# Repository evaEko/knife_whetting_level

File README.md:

# Knife Level BLUNT

A small digital level for knife sharpening. Measures blade surface inclination in real time, displays the angle, and alerts you when you drift from your target sharpening angle.

 Built on MicroPython running on an nRF52840 microcontroller.

Here are some vids:
* [demo vid of the sensor responsiveness](https://imgur.com/a/BOzFHaE).
* [demo vid of the Android app](https://i.imgur.com/QXUnDTm.mp4).
* [foolish idea with 2 displays](https://i.imgur.com/3KEsX2l.mp4)

Commercial use and resale are not permitted.

## License

- Software code, documentation, images, and hardware design files: [CC BY-NC 4.0](LICENSE)
- Third-party subcomponents may use their own license where noted (for example, `kicad/nice-nano-kicad/`)

### Third-party notices

- `kicad/nice-nano-kicad/` is a third-party nice!nano symbol/footprint library bundled with this project.
- The bundled library declares `GNU GPLv3` in `kicad/nice-nano-kicad/README.md`; keep that notice and attribution when redistributing those files.

> **Disclaimer:** This project is provided as-is, without warranty of any kind. The author is not liable for any damage, injury, or loss arising from the use, misuse, or inability to use this project or any hardware built from it.

## Getting Started

1. [Assemble the hardware](docs/HOW_TO_HARDWARE.md)
2. [Flash the firmware](docs/HOW_TO_FIRMWARE.md)
3. Optionally install the Android companion app from the `knife_level_android_apk` workflow artifact

If impatient, go over to [Quick Start](docs/QUICK_START.md).

## Known Issues

- **Android app rescan after restart** — if you power-cycle the level, the Android app will not reconnect automatically; open the app and scan again.
- **Lifted detection is experimental** — the feature that detects when the blade leaves the stone is not reliable and may produce false positives or miss lift events; treat alerts that depend on it as best-effort.

## Acknowledgements

Thanks to [jkorte-dev](https://github.com/jkorte-dev) for publishing the nRF52840 SuperMini/Nice!Nano MicroPython board definitions and UF2 builds used as a flashing base.

Development was assisted by [Claude](https://claude.ai) (Anthropic).

## Features

- **Live sharpening angle** — displays current blade surface inclination in real time on the OLED, rounded to nearest 0.5° with one decimal place
- **Rotation-invariant measurement** — the sensor attaches to the blade with a magnet and can spin freely on the blade face; the reading reports the correct blade angle regardless of how the sensor is rotated on the surface
- **Session calibration** — set the current surface as zero from the on-device settings menu or the Android app
- **Angle setting** — set the current angle as the sharpening angle
- **Visual alert** — display inverts when you drift more than the configured threshold from the target angle; both 0° and 180° orientations are treated as equivalent (knife flipped upside-down is the same angle); threshold supports decimal values (e.g. 0.5°)
- **Preset angle profiles** — define named knives and their angles in `angles.csv`; select them on-device with the top button, with optional restore of the last selected preset after reboot
- **Calibration + presets are independent** — calibrate once to set your physical reference point (zero), then switch between knife presets freely; each preset angle is always displayed relative to the calibration, never compounding
- **Bluetooth companion app** — configure display/behavior settings over BLE, calibrate from the phone, manage preset angles with CRUD operations, and back up/restore presets plus app-exposed settings after reflashing

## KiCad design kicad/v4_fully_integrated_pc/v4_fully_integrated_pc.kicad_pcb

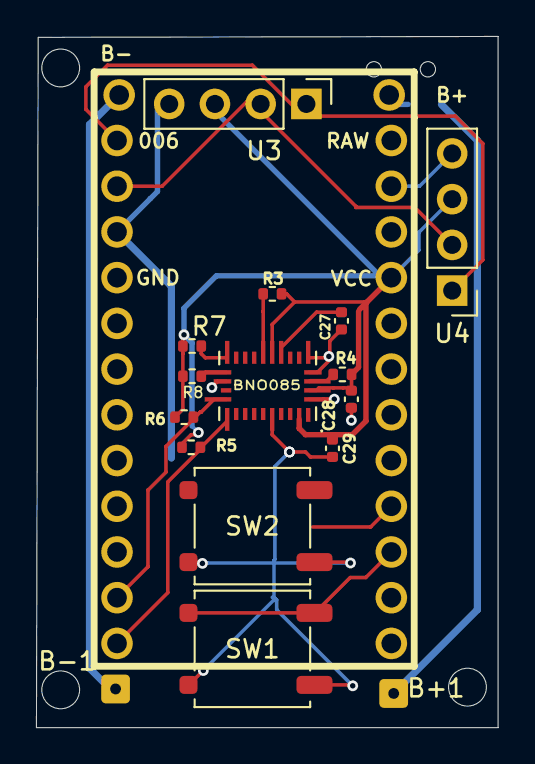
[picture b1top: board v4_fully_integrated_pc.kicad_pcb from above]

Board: 2 copper layers, 25.6 x 38.4 mm, 18 parts (1 on the bottom side), 16 nets.

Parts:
B+1: Conn_01x01; SolderWire-0.1sqmm_1x01_D0.4mm_OD1mm
B-1: Conn_01x01; SolderWire-0.1sqmm_1x01_D0.4mm_OD1mm
BNO085: BNO085; IC_BNO086
C27: 100 nF; C_0402_1005Metric
C28, C29: 100nF; C_0402_1005Metric
R3, R4: 10K; R_0402_1005Metric
R5: 2.2K; R_0402_1005Metric
R6, R7, R8: 4.7K; R_0402_1005Metric
SW1, SW2: SW_Push; SW_Push_1P1T_NO_CK_KSC6xxG
SW_POWER1: SW_SPDT; SW_SPDT_Shouhan_MSK12C02
U1: nice_nano; nice_nano_with_bat_pins
U3, U4: SSD1306_OLED_042; PinHeader_1x04_P2.54mm_Vertical

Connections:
GND: BNO085.2 (GND), BNO085.5 (PS1), BNO085.6 (PS0/WAKE), BNO085.17 (SA0/H_MOSI), BNO085.25 (GNDIO), C27.1, C28.1, C29.1, SW1.2, SW2.2, U1.3 (GND), U1.4 (GND), U1.23 (GND), U3.4 (GND), U4.4 (GND)
unnamed: B+1.1 (Pin_1_1), SW_POWER1.3 (C)
unnamed: B-1.1 (Pin_1_1), U1.26 (B-)
unnamed: BNO085.9 (CAP), C27.2
unnamed: BNO085.15 (ENV_SCL), R7.1
unnamed: BNO085.16 (ENV_SDA), R8.1
unnamed: BNO085.4 (~BOOT), R4.2
unnamed: BNO085.11 (~RST), R3.1
unnamed: SW_POWER1.2 (B), U1.25 (B+)
unnamed: SW1.1, U1.15 (P1.11)
unnamed: SW2.1, U1.16 (P1.13)
unnamed: U1.2 (RX1/P0.08), U3.2 (SCK), U4.2 (SCK)
unnamed: U1.1 (TX0/P0.06), U3.1 (SDA), U4.1 (SDA)
PPH_VCC: BNO085.3 (VDD), BNO085.10 (CLKSEL0), BNO085.28 (VDDIO), C28.2, C29.2, R3.2, R4.1, R5.2, R6.2, R7.2, R8.2, U1.21 (VCC), U3.3 (VCC), U4.3 (VCC)
SCL_BNO: BNO085.19 (H_SCL/SCK/RX), R6.1, U1.11 (P1.04)
SDA_BNO: BNO085.20 (H_SDA/H_MISO/TX), R5.1, U1.12 (P1.06)

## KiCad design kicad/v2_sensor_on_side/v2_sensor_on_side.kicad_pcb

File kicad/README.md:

* v1: sensor is below the mcu: larger footprint
* v2: sensor is on the side and overlaps with the mcu (smaller footprint but thicker)
* v3: same as v2 but with place for a bigger oled
* v4: work in progress: bno085 directly on the board

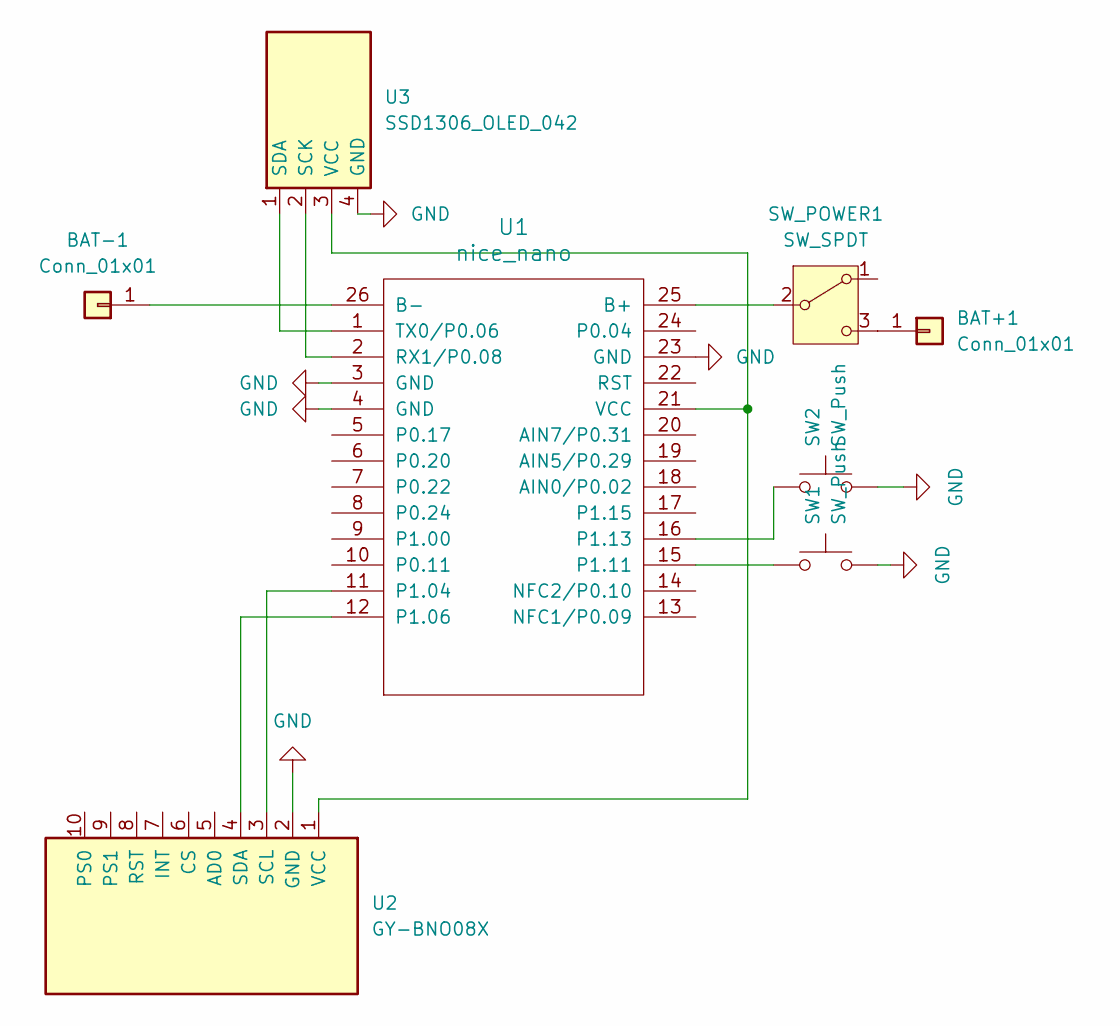
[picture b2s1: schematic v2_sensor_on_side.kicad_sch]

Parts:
BAT+1: Conn_01x01; SolderWire-0.1sqmm_1x01_D0.4mm_OD1mm
BAT-1: Conn_01x01; SolderWire-0.1sqmm_1x01_D0.4mm_OD1mm
SW1, SW2: SW_Push; SW_Push_1P1T_NO_CK_KSC6xxG
SW_POWER1: SW_SPDT; SW_SPDT_Shouhan_MSK12C02
U1: nice_nano; nice_nano_with_bat_pins
U2: GY-BNO08X; PinHeader_1x10_P2.54mm_Vertical
U3: SSD1306_OLED_042; PinHeader_1x04_P2.54mm_Vertical

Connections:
GND: SW1.2, SW2.2, U1.3 (GND), U1.4 (GND), U1.23 (GND), U2.2 (GND), U3.4 (GND)
unnamed: BAT+1.1 (Pin_1_1), SW_POWER1.3 (C)
unnamed: BAT-1.1 (Pin_1_1), U1.26 (B-)
unnamed: SW_POWER1.2 (B), U1.25 (B+)
unnamed: U1.11 (P1.04), U2.3 (SCL)
unnamed: U1.12 (P1.06), U2.4 (SDA)
unnamed: SW1.1, U1.15 (P1.11)
unnamed: SW2.1, U1.16 (P1.13)
unnamed: U1.2 (RX1/P0.08), U3.2 (SCK)
unnamed: U1.1 (TX0/P0.06), U3.1 (SDA)
unnamed: U1.21 (VCC), U2.1 (VCC), U3.3 (VCC)

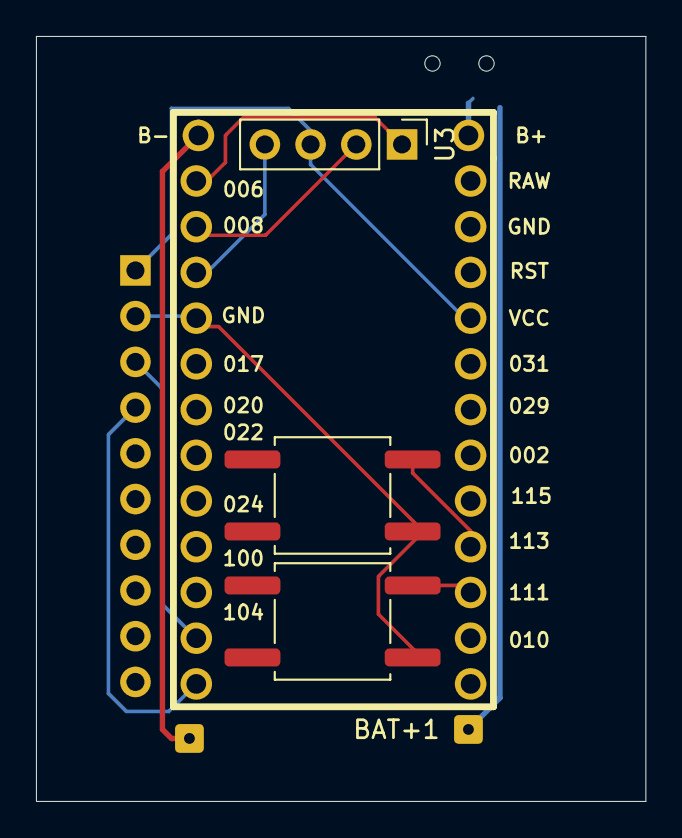
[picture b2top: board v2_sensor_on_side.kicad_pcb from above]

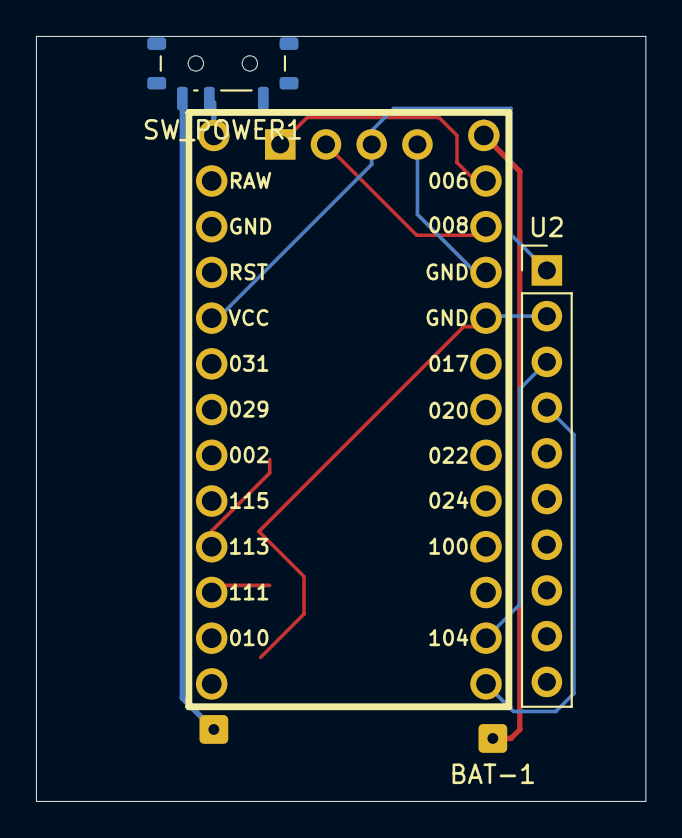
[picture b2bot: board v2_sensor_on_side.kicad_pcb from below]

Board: 2 copper layers, 33.9 x 42.5 mm, 8 parts (4 on the bottom side), 11 nets.

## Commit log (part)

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2026-04-21 new filter: madgwick
2026-04-21 more or less correct
2026-04-21 init
2026-04-21 use pitch,accept upside down position
2026-04-21 improve readme
2026-04-21 add missing dep files, update readme
2026-04-21 fix on not working
2026-04-21 fix on sleep fail
2026-04-21 battery detection for nice nano
2026-04-21 alternative on fix: idel
2026-04-21 tolerate -+ 360
2026-04-21 update nice nano footprint
2026-04-21 started working on new pcb
2026-04-21 add CC BY-NC 4.0 license
2026-04-21 add disclaimer
2026-04-21 add b+ and b- pins
2026-04-21 add todo
2026-04-23 fix b+ and b- traces in pcb
2026-04-23 kicad cleanup
2026-04-23 add flashing script
2026-04-23 code refactoring
2026-04-23 add switch to pcb
2026-04-24 move 2nd button to 113
2026-04-24 huge state refactoring
2026-04-24 stabilize flash script
2026-04-24 implement saved angles
2026-04-24 minors, docs
2026-04-24 clean up hardware doc
2026-04-24 doc cleanup
2026-04-24 add disclaimer and quick start
2026-04-24 added quick start
2026-04-24 update docs
2026-04-24 minor doc updates
2026-04-24 docs cleanup
2026-04-24 add workflow
2026-04-24 trigger workflow only manually
2026-04-24 prepare workflow
2026-04-25 preset the angle relative to calibration
2026-04-25 document the calibration and preset separation
2026-04-25 scaffold for board leveling
2026-04-25 scaffold for board levelling
2026-04-25 add board levelling
2026-04-25 fix board levelling
2026-04-25 update quickstart
2026-04-25 add images
2026-04-25 make intro pic small
2026-04-25 fix docs
2026-04-25 remove assets
2026-04-26 solve licensing
2026-04-26 reboot automatically after levelling change
2026-04-26 fix angle display
2026-04-26 implement angle format select
2026-04-26 persist format setting
2026-04-26 tweak angle display
2026-04-26 allow cal exit
2026-04-26 tweak formatting, config if angle saved
2026-04-26 clear cal on board level
2026-04-26 add note on claude usage
2026-04-26 add custom preset angle
2026-04-26 make build scripts windows compatible
2026-04-26 link to demo vid
2026-04-27 update link to demo vid
2026-04-27 increase oled frequency
2026-04-27 display message when turn on required for charging
2026-04-27 improve charging bypass
2026-04-27 refactor init state
2026-04-27 refactor to proper oop state machine
2026-04-27 improve battery check
2026-04-27 fix varios minors, format
2026-04-27 delay board levelling
2026-04-27 externalize display rate setting
2026-04-27 suport roll and pitch config
2026-04-27 update link to vid
2026-04-27 update gitignores
2026-04-27 add mini pcb version(as printed by aisler as v2.0)
2026-04-27 firmware: add ble support
2026-04-27 allow enable/disable ble
2026-04-27 android: init
2026-04-27 add settings to ble
2026-04-27 fix settings sending
2026-04-27 fix the settings protocol
2026-04-27 android: implement settigs reconnect
2026-04-27 android: implement calibration
2026-04-27 android: add crud angles
2026-04-27 add apk to workflow
2026-04-27 keep scanning for angle if not availble
2026-04-28 android: set angle
2026-04-28 fix setting angle from android app
2026-04-28 load target on start
2026-04-28 fix reconnect
2026-04-28 add launch icon
2026-04-28 fix detection of disconnected
2026-04-28 tidy up the ui of the android app
2026-04-28 update todo
2026-04-28 android: add sound alerts
2026-04-28 tweaking buttons
2026-04-28 minors
2026-04-30 implement custom angle on android
2026-04-30 implement custom angle setting on android
2026-04-30 refactor settings
2026-04-30 get all settings to gear settings
2026-04-30 style main page
2026-04-30 tweak settings style
2026-04-30 change level setting via ble without reboot)
2026-04-30 allow setting bg colors for too high and too low
2026-04-30 adjust bg colors
2026-04-30 tweak the settings
2026-04-30 presentation tweaks
2026-05-01 add back button behavior on preset
2026-05-02 reftrigger level scan for main
2026-05-02 refactor firmware
2026-05-02 remove pitch and roll
2026-05-02 remove roll and pitch from android
2026-05-02 take 3 axis for levelling
2026-05-02 improve deviation
2026-05-04 refactor device god object: split of ble
2026-05-05 implement sampling on board levelling
2026-05-05 calibrate on an even surface
2026-05-05 tidy up firmware
2026-05-06 knife -> Blunt
2026-05-06 improve battery voltage reading
2026-05-06 start case
2026-05-06 remove bogus blender
2026-05-08 update workflow and vid links
2026-05-09 improve board levelling
2026-05-09 fix rotation drift
2026-05-12 add missing files
2026-05-12 refactoring:add battery status
2026-05-12 rectoring: add ble protocol
2026-05-12 refactoring: fix ble
2026-05-12 refactoring: fix button action on ble
2026-05-12 refactoring: fix minors
2026-05-12 refactoring: minors
2026-05-12 refactoring: src_ref -> src
2026-05-12 android: allow custom sound file
2026-05-12 sound alert
2026-05-12 android:fix sound alert setttings
2026-05-12 remove container
2026-05-12 firmware refactoring closed
2026-05-13 various fixes
2026-05-13 add pcb for big display
2026-05-13 android: expose lifted settings
2026-05-13 firmware: move settings out of state
2026-05-14 firmware: spin check with gyro
2026-05-14 misc minor fixes
2026-05-15 thicker traces for battery in pcb
2026-05-15 Update TODO reference to use markdown link
2026-05-15 docs update
2026-05-16 android: restrict permissions
2026-05-16 android: use the restricted permissions in tone player
2026-05-16 update docs on angle calc
2026-05-16 update docs on handling of spinning
2026-05-16 renamed ble advetising name
2026-05-16 update quick start
2026-05-16 firmware: improve battery readings
2026-05-16 kicad: fix project refs
2026-05-16 kicad: tidy up
2026-05-29 add first version of ic
